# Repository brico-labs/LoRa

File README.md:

# LoRa

Repositorio de proyectos relacionados con LoRa

# WorkshopOSHWDem18

Documentación del taller "Introducción a las comunicaciones LoRa y LoRaWAN"

Incluye:

* La presentación del taller
* El proyecto de la BricoLabs ESP8266 LoRa Shield
  * Se partió del trabajo de Gustavo Reynaga y su [WeMos_Shield_BricoLabs](https://github.com/hulkco/LoRa/tree/master/WeMos_Shield_Bricolabs) y fué completamente modificado su pinado para adaptarse al taller
* Los ejemplos utilizados durante el taller
  * LoRa P2P
    * Basado en el ejemplo de la librería [arduino-LoRa](https://github.com/sandeepmistry/arduino-LoRa)
  * TTN Node
    * Basado en el ejemplo de la librería [arduino-lmic](https://github.com/matthijskooijman/arduino-lmic)
  * TTN Gateway with Sensors
    * Basado en el increible proyecto [ESP-1ch-Gateway-v5.0](https://github.com/things4u/ESP-1ch-Gateway-v5.0)

### Prerequisitos

El taller se realizó con la última versión disponible de Arduino en su momento 1.8.7

### Instalación
Los ejemplos son sketchs de arduino de otros autores modificados para funcionar con nuestra shield y el taller, incluyen las librerías utilizadas que compilan sin errores.

La BricoLabs ESP8266 LoRa Shield presenta un problema no detectado hasta su montaje. Los pines D3 y D4 son utilizados por el módulo LoRa y al estar conectados impiden en muchos casos tanto la programación como el boot del ESP8266. Para el taller se ha evitado la conexión entre estos pines de la shield y el ESP8266. Con esta modificación los ejemplos parecen funcionar sin mucho problema.

También para el taller se ha cortado el solder jumper JP1 quedando desconectado el dio2 del módulo LoRa y el pin D0 del ESP8266.

### Materiales taller

* BricoLabs ESP8266 LoRa Shield
  * Módulo LoRa RFM95W 868MHz: https://goo.gl/Lq5xBn o https://goo.gl/x9Ruqk
  * Conector antena SMA: https://goo.gl/uX1qVK
  * Antena SMA 868MHz https://goo.gl/3MmXzr
  * Condensador 1uF 0805: https://goo.gl/9gNtP3
  * Condensador 10uF 0805: https://goo.gl/FJRFJw
* ESP8266 WeMos D1 mini  https://goo.gl/JqPN6Y
* Shield Temperatura y humedad SHT30 https://goo.gl/2b3S51

## Contribuye!

Si ves algun error o quieres contribuir con algun ejemplo o modificación envíanos un pull request!

## Autores
Proyectos Originales:
* **Gustavo Reynaga** - *WeMos_Shield_BricoLabs* - [hulkco](https://github.com/hulkco)

* **Sandeep Mistry** - *arduino-LoRa* - [sandeepmistry](https://github.com/sandeepmistry)

* **Matthijs Kooijman** - *arduino-lmic* - [matthijskooijman](https://github.com/matthijskooijman)

* **Maarten Westenberg** - *ESP-1ch-Gateway-v5.0* - [things4u](https://github.com/things4u)

Modificaciones y ñapas:
* **Alejandro Taracido @TCRobotics** - * BricoLabs ESP8266 LoRa Shield, taller, y modificación de ejemplos * - [TCRobotics](https://github.com/TCRobotics)

Mira también la lista de [contribuidores](https://github.com/your/project/contributors) que participaron en el proyecto.

## Licencia

Cada ejemplo está licenciado según las licencias de los autores

## Grupo de Telegram
Después del taller se ha creado un grupo de Telegram para los interesados en TTN y LoRa de Coruña https://t.me/joinchat/AGoVpU_xfHY2CJOtXUelTg

## Agradecimientos

* A los autores de los proyectos utilizados para este taller, sin su trabajo, todo esto no sería posible.
* A TTN (The Things Network) y su comunidad, por su red y todo lo que he podido aprender.
* A BricoLabs por la organización de la OSHWDem y la ayuda en el taller y su aprovisionamiento de materiales.
* A Victor (Benchosei), Óscar (dev4migo) y Sergio (Salvari) por su ayuda con los problemas detectados el día anterior de taller xD
* A Victor (Benchosei), Óscar (dev4migo), Rafa (caligari), Santi Castro y Carlos Miranda por su ayuda durante la realización del taller.
* A Manuel Miramontes por su ayuda en el deploy de los gateways TTN de BricoLabs.
* A los asistentes del taller, por aguantarme y conseguir los objetivos del taller!

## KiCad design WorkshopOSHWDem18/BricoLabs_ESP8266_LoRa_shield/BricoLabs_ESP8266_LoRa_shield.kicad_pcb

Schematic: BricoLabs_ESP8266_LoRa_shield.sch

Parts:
A2: ANT; SMA_EDGELAUNCH_UFL
C1: 1u; C_0805_2012Metric_Pad1.29x1.40mm_HandSolder
C2: 10u; C_0805_2012Metric_Pad1.29x1.40mm_HandSolder
J0: Conn_01x01; Pin_D0.9mm_L10.0mm_W2.4mm_FlatFork
J1, J2: Conn_01x02; PinHeader_1x02_P2.54mm_Vertical
JP1: Jumper_NC_Dual; SolderJumper-3_P1.3mm_Bridged12_RoundedPad1.0x1.5mm
P1, P2: CONN_01X08; D1_mini_Pin_Header
U1: RFM95W-915S2; HOPERF_RFM9XW_SMD_WeMos

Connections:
/+3.3V: C1.1, C2.1, P2.1, U1.13 (3.3V)
/+5V: P1.1
/A0: P2.7
/D0: JP1.2, P2.6
/D1: P1.6
/D2: P1.5
/D3: P1.4, U1.14 (DIO0)
/D4: P1.3, U1.15 (DIO1)
/D5: P2.5, U1.4 (SCK)
/D6: P2.4, U1.2 (MISO)
/D7: P2.3, U1.3 (MOSI)
/D8: P2.2, U1.5 (NSS)
/DIO2: JP1.1, U1.16 (DIO2)
/DIO3: J2.2, U1.11 (DIO3)
/DIO4: J2.1, U1.12 (DIO4)
/DIO5: J1.1, U1.7 (DIO5)
/GND: A2.2, A2.3, A2.4, A2.5, C1.2, C2.2, P1.2, U1.1 (GND), U1.8 (GND), U1.10 (GND)
/RFM_RST: J1.2, U1.6 (RESET)
/RST: JP1.3, P2.8
/RX: P1.7
/TX: P1.8
unnamed: A2.1, J0.1, U1.9 (ANT)

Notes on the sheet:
GPIO2
GPIO0
GPIO4
GPIO5
GPIO15
GPIO13
GPIO12
GPIO14
GPIO16
D1 Mini Shield

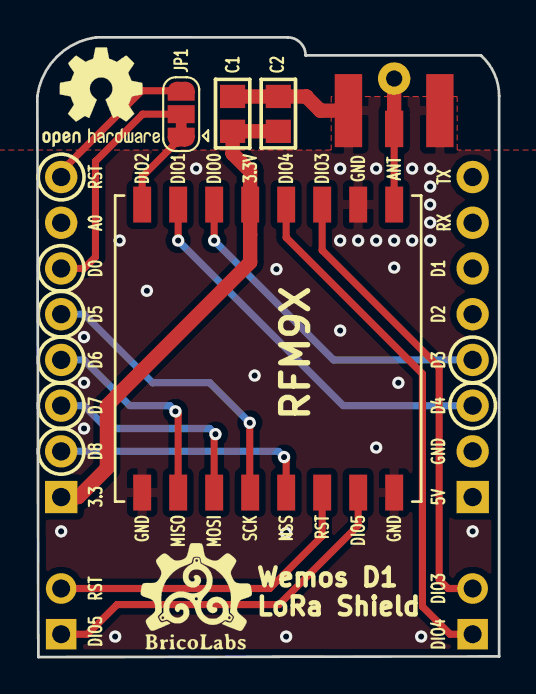
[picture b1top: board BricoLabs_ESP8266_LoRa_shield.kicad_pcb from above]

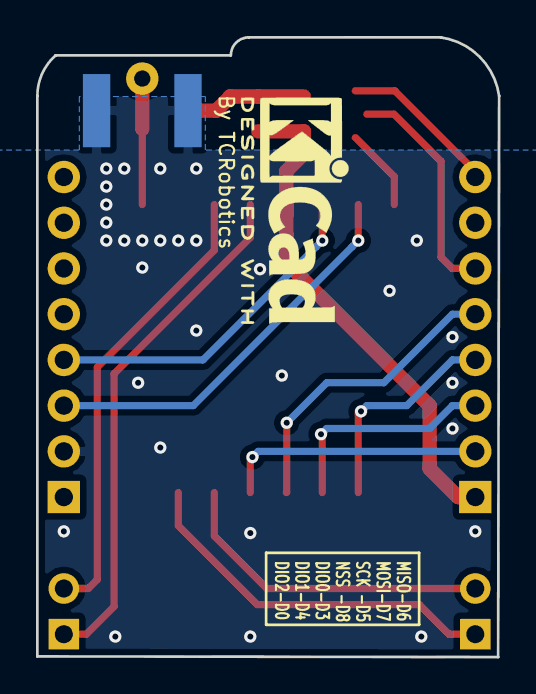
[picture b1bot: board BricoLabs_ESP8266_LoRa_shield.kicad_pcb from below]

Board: 2 copper layers, 25.7 x 34.4 mm, 10 parts (2 on the bottom side), 16 nets.

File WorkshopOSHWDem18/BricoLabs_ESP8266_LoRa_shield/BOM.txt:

P1, P2: 8 pin female header long pins
U1: RFM95W //https://goo.gl/Lq5xBn or https://goo.gl/x9Ruqk
C1: Capacitor 1uF 0805 //https://goo.gl/9gNtP3
C2: Capacitor 10uF 0805 //https://goo.gl/FJRFJw
A2: SMA antenna connector //https://goo.gl/uX1qVK
J1,J2: 2pin female header

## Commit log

2018-10-13 Added Slides
2018-10-14 Added LoRa P2P project and Libraries
2018-10-14 Added TTN node project and libraries
2018-10-14 Added TTN Gateway with sensors project and project libraries
2018-10-14 Added BricoLabs ESP8266 LoRa Shield KiCAD Project
2018-10-14 Added ESP8266 Arduino install link
2018-10-14 Add schematic in PDF
2018-10-14 Add BOM
2018-10-16 Added link to Carlos Miranda´s vídeo
2019-07-21 TTN-node with WemosLora hack, compilable with platformio.
2019-07-21 Image of lora-wemos hack.
2019-07-21 Some typos.
